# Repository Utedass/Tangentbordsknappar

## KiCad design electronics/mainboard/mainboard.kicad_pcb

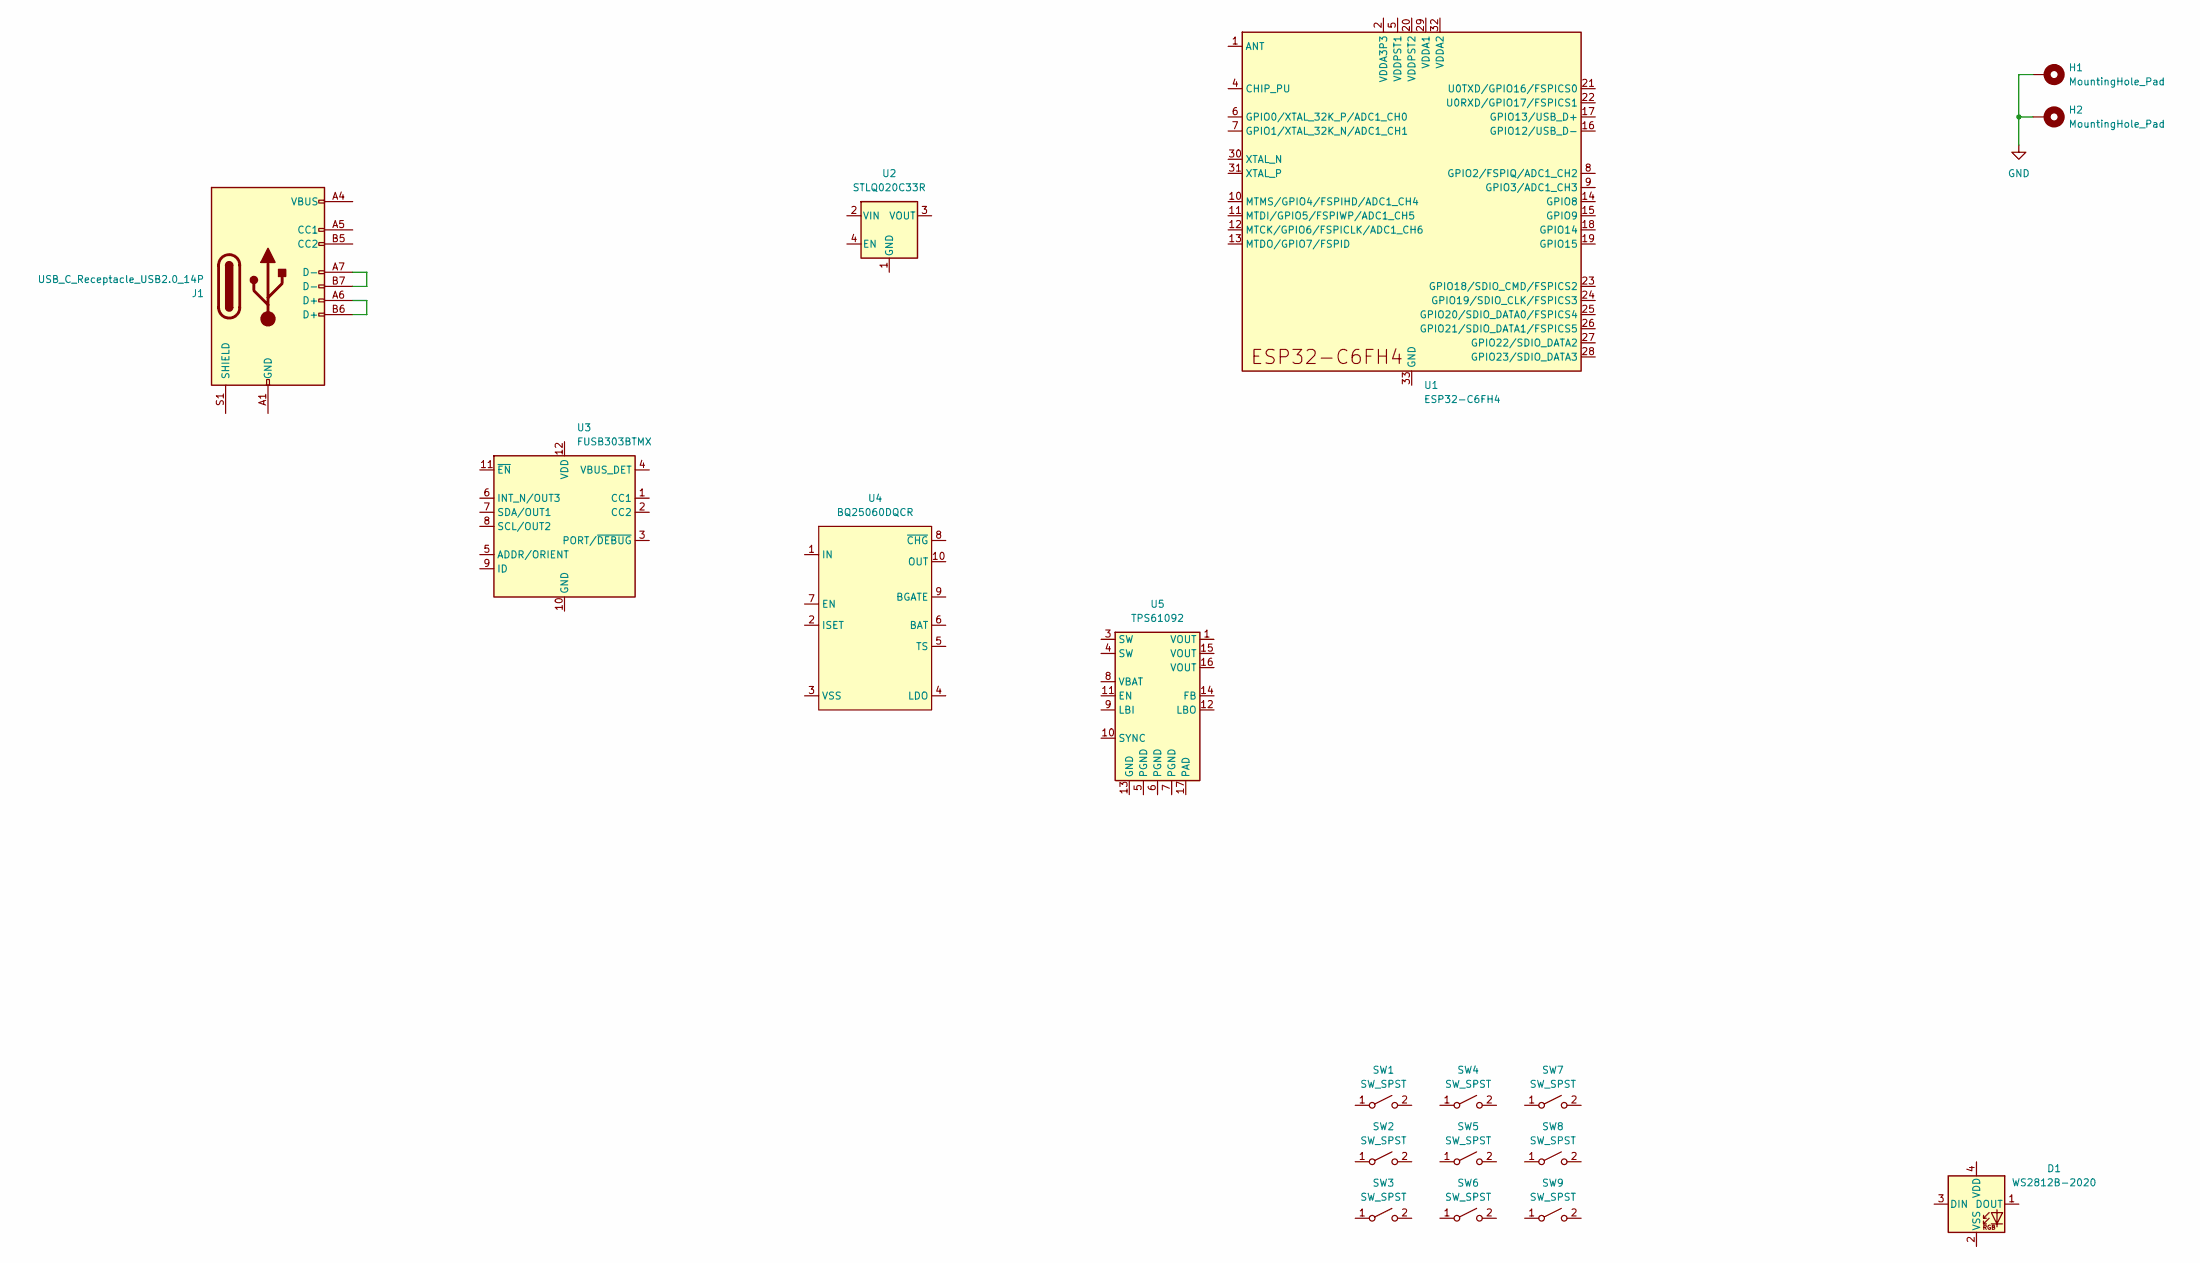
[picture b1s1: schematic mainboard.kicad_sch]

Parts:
D1: WS2812B-2020; LED_WS2812B-2020_PLCC4_2.0x2.0mm
H1, H2: MountingHole_Pad; MountingHole_3.2mm_M3_Pad_Via
J1: USB_C_Receptacle_USB2.0_14P; USB_C_Receptacle_GCT_USB4085
SW1, SW2, SW3, SW4, SW5, SW6, SW7, SW8, SW9: SW_SPST; SW_Cherry_MX_PCB
U1: ESP32-C6FH4; QFN-32-1EP_5x5mm_P0.5mm_EP3.6x3.6mm
U2: STLQ020C33R; SOT-23-5
U3: FUSB303BTMX; Texas_X2QFN-12_1.6x1.6mm_P0.4mm
U4: BQ25060DQCR; WSON-10-1EP_2x3mm_P0.5mm_EP0.84x2.4mm
U5: TPS61092; Texas_RSA_VQFN-16-1EP_4x4mm_P0.65mm_EP2.7x2.7mm_ThermalVias

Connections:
GND: H1.1, H2.1
unnamed: J1.A6 (D+), J1.B6 (D+)
unnamed: J1.A7 (D-), J1.B7 (D-)
unnamed: J1.A1 (GND), J1.A12 (GND), J1.B1 (GND), J1.B12 (GND)
unnamed: J1.A4 (VBUS), J1.A9 (VBUS), J1.B4 (VBUS), J1.B9 (VBUS)
unnamed: U1.2 (VDDA3P3), U1.3 (VDDA3P3)

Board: 2 copper layers, 18 parts (6 on the bottom side), 6 nets, no tracks yet.

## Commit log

2026-01-22 Extend fitting-sleeve by .2
2026-01-22 Add beginning of a keybox
2026-01-23 Make fitting sleve longer
2026-01-24 Add screw holes in intersections
2026-01-24 Add keyswitch model. Add dovetail to plate. Create assembly.
2026-01-24 Add side to plate
2026-01-25 Don't remmember...
2026-01-25 Update file structure
2026-01-25 Close the box
2026-01-25 Add USB hole. Start kicad project.
2026-01-26 Add tiny tolerance to bottom-lid for PCB thickness
2026-01-26 Add more tolerance to dovetail joint.
2026-01-26 Remove tolerances, good fit without. Add locking notch.
2026-01-27 Add gitattributes. Layout position of switches and board outline
2026-01-31 Add system diagram. Add project symbol library. Add fundamental components to schematic.
2026-02-01 Add drawio to always have lf
2026-02-01 Fix boardcut.
2026-02-01 Ignore lock file. Change switch footprint to exclude spacing. Change hole footprint to include pad.
2026-02-08 Move system diagram to design description folder
2026-02-08 Add latex-files to gitignore
2026-02-14 Add beginning of template for design description
2026-02-15 Update parts in system diagram according to #1, #2 and #3
2026-02-15 Begin actual description document
2026-02-15 Add more sections and update figure naming.
2026-02-17 Update design description and its class.
2026-04-07 Add \designproblem command.
2026-04-07 Add frame to design problems
2026-04-07 Add todomessages and make it work with multicols envirionment.
2026-04-07 Add requirements and chapter explaining this.
2026-04-07 Remove reduntant pdftex argument.
2026-04-09 Fill out info regarding charger.
2026-04-10 Fill out the charger chapter more.
